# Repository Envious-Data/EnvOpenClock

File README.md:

# Env-OpenClock
 A fancy lil clock using 8x LTP-305s and a Raspberry Pi Pico.

## Information
This clock features a DS3231 but it doesnt have its own onboard battery management meaning its meant to have constant power but there is nothing stopping anyone from soldering something like a pico lipo shim to the back of the PCB. The RTC is mainly for convenience.

There are 4 buttons and a switch, The switch is meant for Summer time adjustment and the 4 buttons are for setting the time or alarm.

## Implemented Features
- Time Setting
- Date Mode

## Planned software features
(Some ideas, may not get implemented)
- Animated text to show time has been set?
- Animated Transition to menus?
- A menu system
- Alarm system
- Text Marquee modes

## Planned Hardware features
In the current version of the board there is a a DS3231 w/ CR1220 battery, Raspberry pi pico, 4x tactile buttons, 4x IS31FL37s, a small piezo speaker and amp and obviously the 8x LTP305 sockets.

We'd like to change this to have easier to press buttons, a larger battery holder, the speaker may not get re-implemented, we'll see when we decide to move toward finalizing the design and preparing for order. Keep in mind that TIL305s have been discontinued for a long time and LTP305s are now discontinued and hard to get so we'll substitute our own "DIY305" which is a dip14 sized PCB with standard headers and 0402 leds but we have made a 0201 version but may not use it due to cost.

## Hardware
I designed the board in KiCad, you can use various plugins to generate production files for your chosen PCB FAB
Some aspects may change but I generally intend to keep the formfactor the same and all the components on one side for cheaper manufacturing.

since the board uses 8x LTP305s you can also display the date instead of the time, the RTC does store the date as well as the time, currently as of writing this the firmware only displays the current time stored on the DS3231 RTC, but the main planned features are day/date/time setting and then goals can expand. Its possible to add text marquee too.

## PCBWAY

[PCBWAY](http://pcbway.com) Kindly sponsored a batch of PCBs of which you can see a video of the board working below

https://github.com/Envious-Data/Env-OpenClock/assets/5001879/fdac6cdb-803a-443c-b91d-f5f40f54c28f

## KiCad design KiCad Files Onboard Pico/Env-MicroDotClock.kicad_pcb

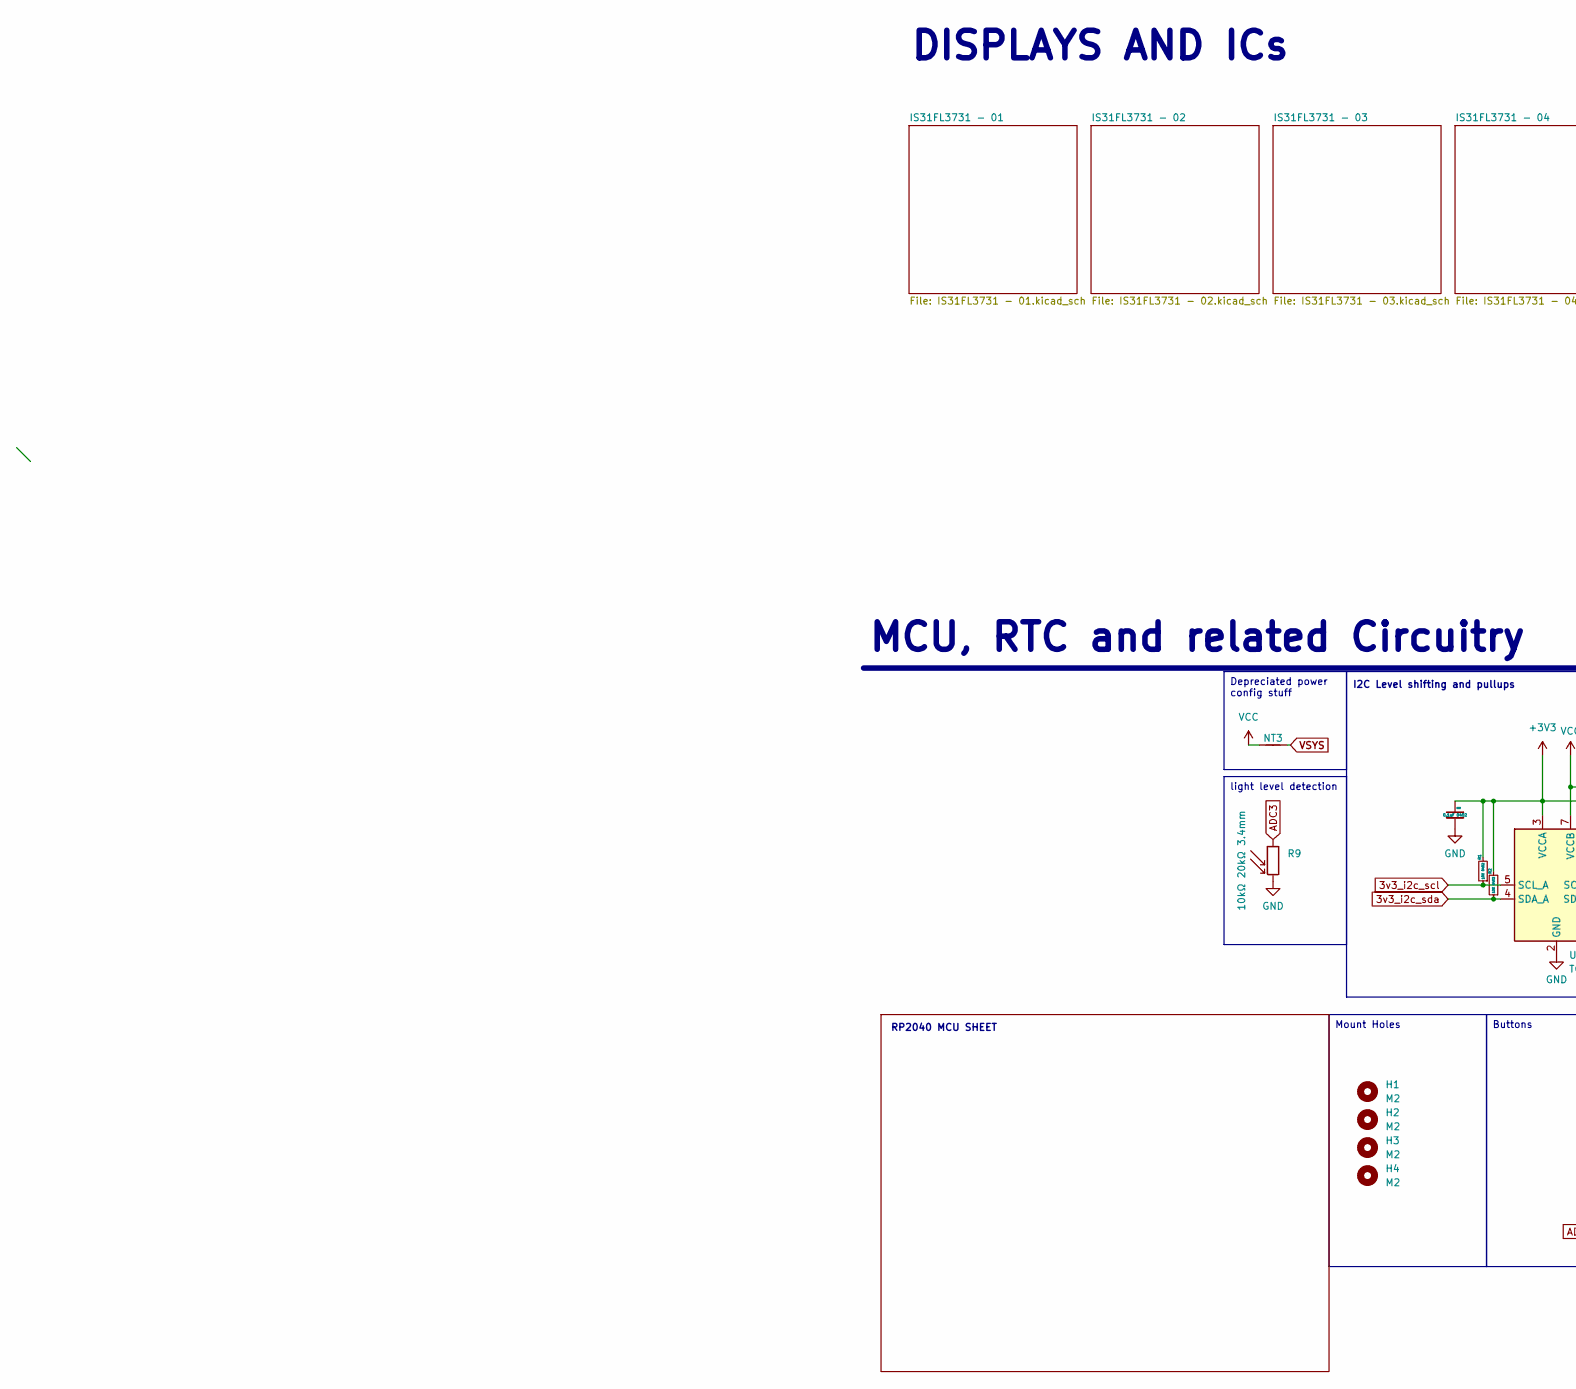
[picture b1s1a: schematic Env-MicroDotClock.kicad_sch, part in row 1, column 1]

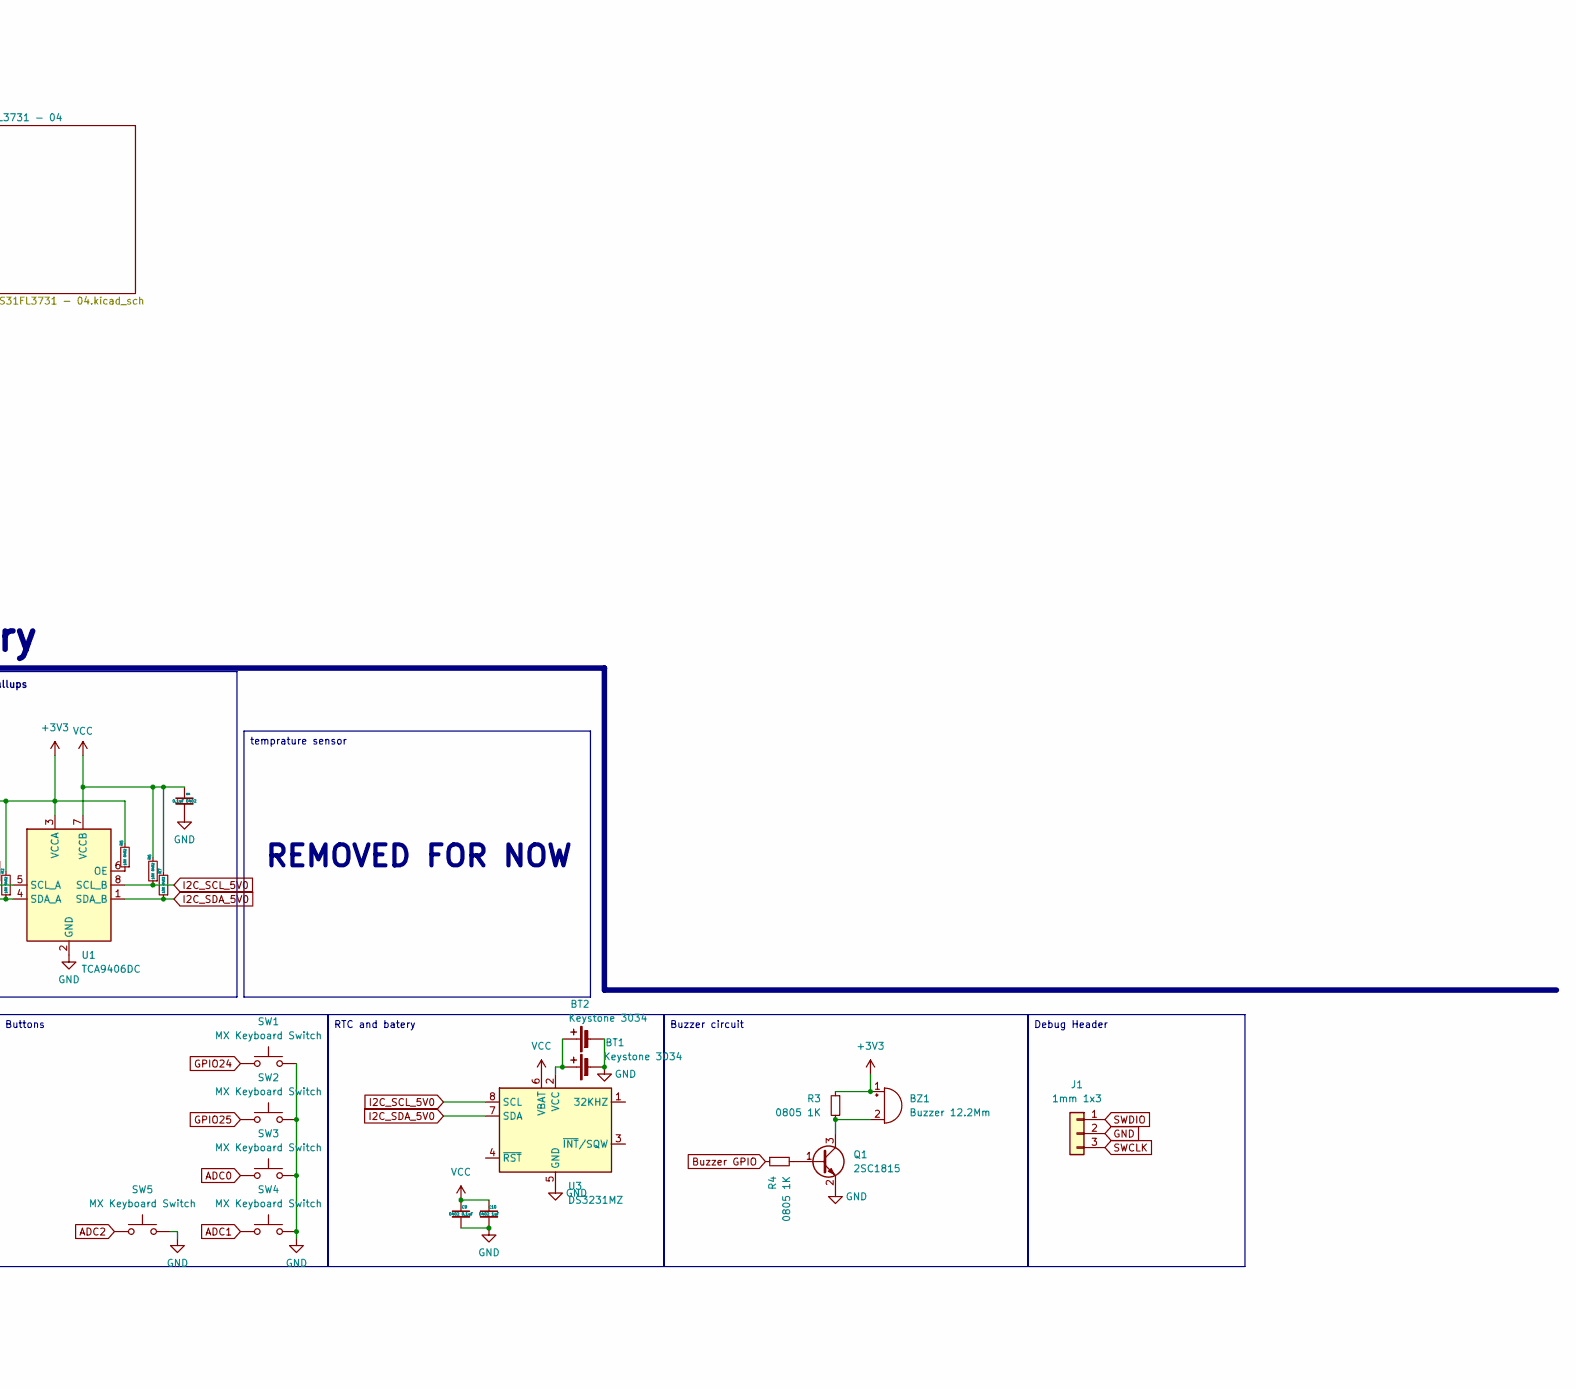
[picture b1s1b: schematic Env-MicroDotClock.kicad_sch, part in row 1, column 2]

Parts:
BT1, BT2: Keystone 3034; BatteryHolder_Keystone_3034_1x20mm
BZ1: Buzzer 12.2Mm; Buzzer_TDK_PS1240P02BT_D12.2mm_H6.5mm
C9: 0402 0.1uF; C_0402_1005Metric
C10: 0402 1uF; C_0402_1005Metric
C33, C34: 0.1uF 0402; C_0402_1005Metric
H1, H2, H3, H4: M2; MountingHole_2.2mm_M2
J1: 1mm 1x3; PinHeader_1x03_P1.00mm_Vertical
NT3: NetTie_2; NetTie-2_THT_Pad0.3mm
Q1: 2SC1815; SOT-23
R1, R2, R5, R6, R7: 10K 0402; R_0402_1005Metric
R3, R4: 0805 1K; R_0805_2012Metric
R9: 10kΩ 20kΩ 3.4mm; R_LDR_5.1x4.3mm_P3.4mm_Vertical
SW1, SW2, SW3, SW4, SW5: MX Keyboard Switch; SW_Cherry_MX_1.00u_PCB
U1: TCA9406DC; VSSOP-8_2.3x2mm_P0.5mm
U3: DS3231MZ; SOIC-8_3.9x4.9mm_P1.27mm

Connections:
3v3_i2c_scl: R1.1, U1.5 (SCL_A); also elsewhere on the board
3v3_i2c_sda: R2.1, U1.4 (SDA_A); also elsewhere on the board
+3V3: BZ1.1 (-), C33.1, R1.2, R2.2, R3.1, R5.2, U1.3 (VCCA); also elsewhere on the board
ADC0: SW3.1; also elsewhere on the board
ADC1: SW4.1; also elsewhere on the board
ADC2: SW5.1; also elsewhere on the board
ADC3: R9.1; also elsewhere on the board
Buzzer GPIO: R4.1; also elsewhere on the board
GND: BT1.2 (-), BT2.2 (-), C9.2, C10.2, C33.2, C34.2, J1.2, Q1.2 (E), R9.2, SW1.2, SW2.2, SW3.2, SW4.2, SW5.2, U1.2 (GND), U3.5 (GND); also elsewhere on the board
GPIO24: SW1.1; also elsewhere on the board
GPIO25: SW2.1; also elsewhere on the board
I2C_SCL_5V0: R6.1, U1.8 (SCL_B), U3.8 (SCL); also elsewhere on the board
I2C_SDA_5V0: R7.1, U1.1 (SDA_B), U3.7 (SDA); also elsewhere on the board
unnamed: BT1.1 (+), BT2.1 (+), U3.2 (VCC)
unnamed: BZ1.2 (+), Q1.3 (C), R3.2
unnamed: Q1.1 (B), R4.2
unnamed: R5.1, U1.6 (OE)
SWCLK: J1.3; also elsewhere on the board
SWDIO: J1.1; also elsewhere on the board
VCC: C9.1, C10.1, C34.1, NT3.1, R6.2, R7.2, U1.7 (VCCB), U3.6 (VBAT); also elsewhere on the board
VSYS: NT3.2; also elsewhere on the board

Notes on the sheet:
light level detection
RTC and batery
Mount Holes
Depreciated power config stuff
Buzzer circuit
Debug Header
Buttons
temprature sensor
DISPLAYS AND ICs
MCU, RTC and related Circuitry
RP2040 MCU SHEET
I2C Level shifting and pullups
REMOVED FOR NOW

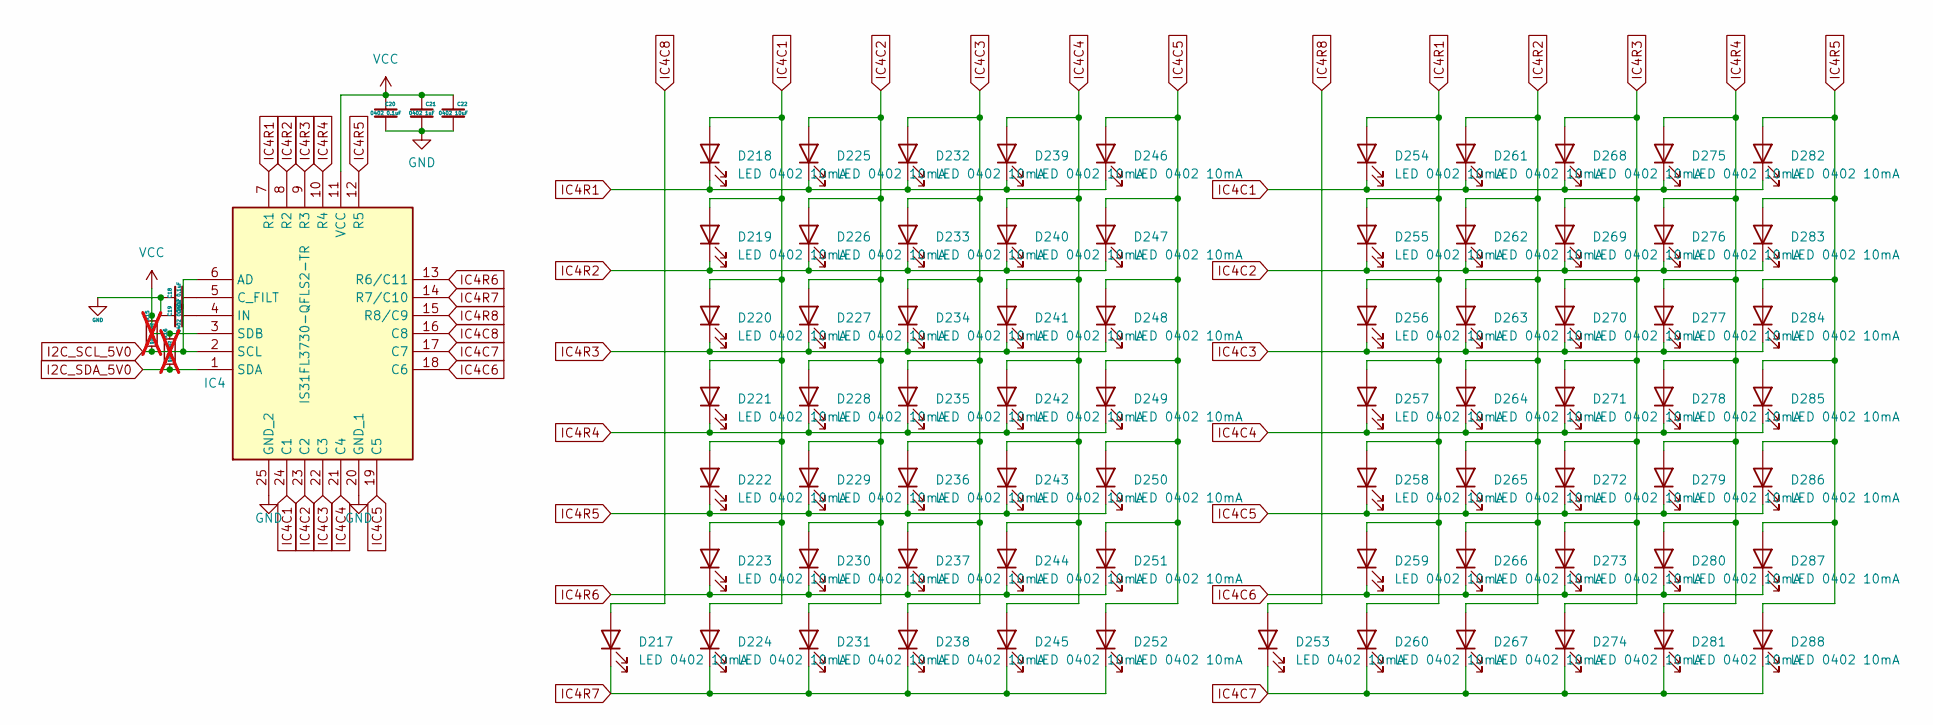
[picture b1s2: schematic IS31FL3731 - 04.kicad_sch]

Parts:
C18, C20: 0402 0.1uF; C_0402_1005Metric
C19: 0402 0.22uF; C_0402_1005Metric
C21: 0402 1uF; C_0402_1005Metric
C22: 0402 10uF; C_0402_1005Metric
D217, D218, D219, D220, D221, D222, D223, D224, D225, D226, D227, D228, D229, D230, D231, D232, D233, D234, D235, D236, D237, D238, D239, D240, D241, D242, D243, D244, D245, D246, D247, D248, D249, D250, D251, D252, D253, D254, D255, D256, D257, D258, D259, D260, D261, D262, D263, D264, D265, D266, D267, D268, D269, D270, D271, D272, D273, D274, D275, D276, D277, D278, D279, D280, D281, D282, D283, D284, D285, D286, D287, D288: LED 0402 10mA; LED_0402_1005Metric
IC4: IS31FL3730-QFLS2-TR; QFN-24-1EP_4x4mm_P0.5mm_EP2.6x2.6mm_ThermalVias; Mouser Part Number 870-IS31FL3730QFLS2R
R15, R16: 10K 0402; R_0402_1005Metric; not fitted

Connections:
GND: C18.1, C19.1, C20.2, C21.2, C22.2, IC4.20 (GND_1), IC4.25 (GND_2); also elsewhere on the board
I2C_SCL_5V0: IC4.2 (SCL), IC4.6 (AD), R15.1; also elsewhere on the board
I2C_SDA_5V0: IC4.1 (SDA), R16.1; also elsewhere on the board
IC4C1: D218.2 (A), D219.2 (A), D220.2 (A), D221.2 (A), D222.2 (A), D223.2 (A), D224.2 (A), D254.1 (K), D261.1 (K), D268.1 (K), D275.1 (K), D282.1 (K), IC4.24 (C1)
IC4C2: D225.2 (A), D226.2 (A), D227.2 (A), D228.2 (A), D229.2 (A), D230.2 (A), D231.2 (A), D255.1 (K), D262.1 (K), D269.1 (K), D276.1 (K), D283.1 (K), IC4.23 (C2)
IC4C3: D232.2 (A), D233.2 (A), D234.2 (A), D235.2 (A), D236.2 (A), D237.2 (A), D238.2 (A), D256.1 (K), D263.1 (K), D270.1 (K), D277.1 (K), D284.1 (K), IC4.22 (C3)
IC4C4: D239.2 (A), D240.2 (A), D241.2 (A), D242.2 (A), D243.2 (A), D244.2 (A), D245.2 (A), D257.1 (K), D264.1 (K), D271.1 (K), D278.1 (K), D285.1 (K), IC4.21 (C4)
IC4C5: D246.2 (A), D247.2 (A), D248.2 (A), D249.2 (A), D250.2 (A), D251.2 (A), D252.2 (A), D258.1 (K), D265.1 (K), D272.1 (K), D279.1 (K), D286.1 (K), IC4.19 (C5)
IC4C6: D259.1 (K), D266.1 (K), D273.1 (K), D280.1 (K), D287.1 (K), IC4.18 (C6)
IC4C7: D253.1 (K), D260.1 (K), D267.1 (K), D274.1 (K), D281.1 (K), D288.1 (K), IC4.17 (C7)
IC4C8: D217.2 (A), IC4.16 (C8)
IC4R1: D218.1 (K), D225.1 (K), D232.1 (K), D239.1 (K), D246.1 (K), D254.2 (A), D255.2 (A), D256.2 (A), D257.2 (A), D258.2 (A), D259.2 (A), D260.2 (A), IC4.7 (R1)
IC4R2: D219.1 (K), D226.1 (K), D233.1 (K), D240.1 (K), D247.1 (K), D261.2 (A), D262.2 (A), D263.2 (A), D264.2 (A), D265.2 (A), D266.2 (A), D267.2 (A), IC4.8 (R2)
IC4R3: D220.1 (K), D227.1 (K), D234.1 (K), D241.1 (K), D248.1 (K), D268.2 (A), D269.2 (A), D270.2 (A), D271.2 (A), D272.2 (A), D273.2 (A), D274.2 (A), IC4.9 (R3)
IC4R4: D221.1 (K), D228.1 (K), D235.1 (K), D242.1 (K), D249.1 (K), D275.2 (A), D276.2 (A), D277.2 (A), D278.2 (A), D279.2 (A), D280.2 (A), D281.2 (A), IC4.10 (R4)
IC4R5: D222.1 (K), D229.1 (K), D236.1 (K), D243.1 (K), D250.1 (K), D282.2 (A), D283.2 (A), D284.2 (A), D285.2 (A), D286.2 (A), D287.2 (A), D288.2 (A), IC4.12 (R5)
IC4R6: D223.1 (K), D230.1 (K), D237.1 (K), D244.1 (K), D251.1 (K), IC4.13 (R6/C11)
IC4R7: D217.1 (K), D224.1 (K), D231.1 (K), D238.1 (K), D245.1 (K), D252.1 (K), IC4.14 (R7/C10)
IC4R8: D253.2 (A), IC4.15 (R8/C9)
unnamed: C18.2, IC4.5 (C_FILT)
unnamed: C19.2, IC4.4 (IN)
VCC: C20.1, C21.1, C22.1, IC4.3 (SDB), IC4.11 (VCC), R15.2, R16.2; also elsewhere on the board

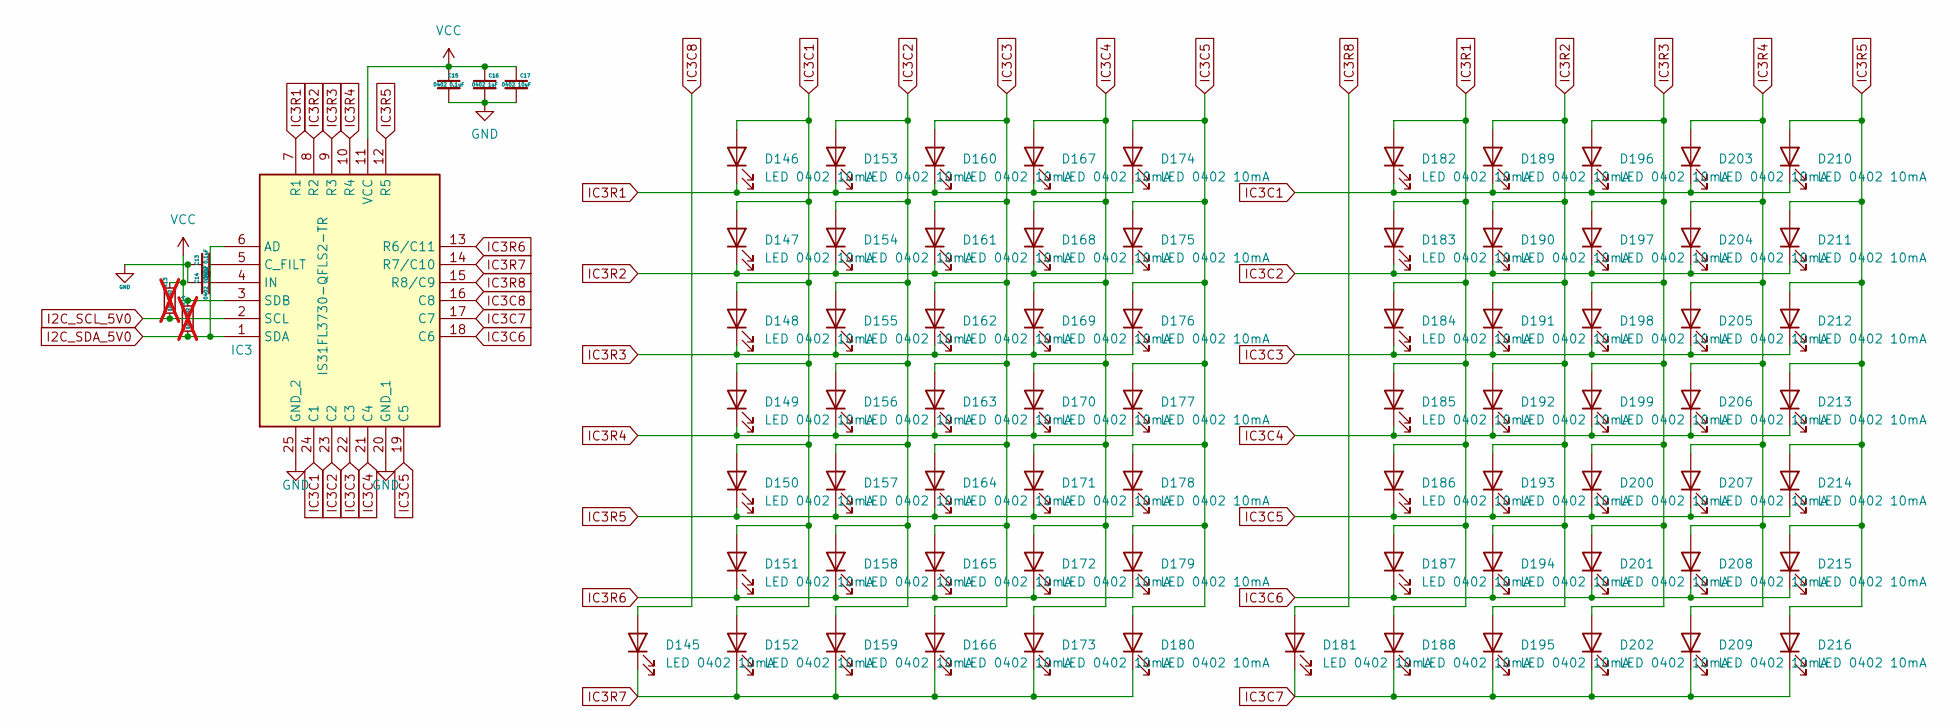
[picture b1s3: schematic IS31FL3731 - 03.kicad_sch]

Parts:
C13, C15: 0402 0.1uF; C_0402_1005Metric
C14: 0402 0.22uF; C_0402_1005Metric
C16: 0402 1uF; C_0402_1005Metric
C17: 0402 10uF; C_0402_1005Metric
D145, D146, D147, D148, D149, D150, D151, D152, D153, D154, D155, D156, D157, D158, D159, D160, D161, D162, D163, D164, D165, D166, D167, D168, D169, D170, D171, D172, D173, D174, D175, D176, D177, D178, D179, D180, D181, D182, D183, D184, D185, D186, D187, D188, D189, D190, D191, D192, D193, D194, D195, D196, D197, D198, D199, D200, D201, D202, D203, D204, D205, D206, D207, D208, D209, D210, D211, D212, D213, D214, D215, D216: LED 0402 10mA; LED_0402_1005Metric
IC3: IS31FL3730-QFLS2-TR; QFN-24-1EP_4x4mm_P0.5mm_EP2.6x2.6mm_ThermalVias; Mouser Part Number 870-IS31FL3730QFLS2R
R13, R14: 10K 0402; R_0402_1005Metric; not fitted

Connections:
GND: C13.1, C14.1, C15.2, C16.2, C17.2, IC3.20 (GND_1), IC3.25 (GND_2); also elsewhere on the board
I2C_SCL_5V0: IC3.2 (SCL), R13.1; also elsewhere on the board
I2C_SDA_5V0: IC3.1 (SDA), IC3.6 (AD), R14.1; also elsewhere on the board
IC3C1: D146.2 (A), D147.2 (A), D148.2 (A), D149.2 (A), D150.2 (A), D151.2 (A), D152.2 (A), D182.1 (K), D189.1 (K), D196.1 (K), D203.1 (K), D210.1 (K), IC3.24 (C1)
IC3C2: D153.2 (A), D154.2 (A), D155.2 (A), D156.2 (A), D157.2 (A), D158.2 (A), D159.2 (A), D183.1 (K), D190.1 (K), D197.1 (K), D204.1 (K), D211.1 (K), IC3.23 (C2)
IC3C3: D160.2 (A), D161.2 (A), D162.2 (A), D163.2 (A), D164.2 (A), D165.2 (A), D166.2 (A), D184.1 (K), D191.1 (K), D198.1 (K), D205.1 (K), D212.1 (K), IC3.22 (C3)
IC3C4: D167.2 (A), D168.2 (A), D169.2 (A), D170.2 (A), D171.2 (A), D172.2 (A), D173.2 (A), D185.1 (K), D192.1 (K), D199.1 (K), D206.1 (K), D213.1 (K), IC3.21 (C4)
IC3C5: D174.2 (A), D175.2 (A), D176.2 (A), D177.2 (A), D178.2 (A), D179.2 (A), D180.2 (A), D186.1 (K), D193.1 (K), D200.1 (K), D207.1 (K), D214.1 (K), IC3.19 (C5)
IC3C6: D187.1 (K), D194.1 (K), D201.1 (K), D208.1 (K), D215.1 (K), IC3.18 (C6)
IC3C7: D181.1 (K), D188.1 (K), D195.1 (K), D202.1 (K), D209.1 (K), D216.1 (K), IC3.17 (C7)
IC3C8: D145.2 (A), IC3.16 (C8)
IC3R1: D146.1 (K), D153.1 (K), D160.1 (K), D167.1 (K), D174.1 (K), D182.2 (A), D183.2 (A), D184.2 (A), D185.2 (A), D186.2 (A), D187.2 (A), D188.2 (A), IC3.7 (R1)
IC3R2: D147.1 (K), D154.1 (K), D161.1 (K), D168.1 (K), D175.1 (K), D189.2 (A), D190.2 (A), D191.2 (A), D192.2 (A), D193.2 (A), D194.2 (A), D195.2 (A), IC3.8 (R2)
IC3R3: D148.1 (K), D155.1 (K), D162.1 (K), D169.1 (K), D176.1 (K), D196.2 (A), D197.2 (A), D198.2 (A), D199.2 (A), D200.2 (A), D201.2 (A), D202.2 (A), IC3.9 (R3)
IC3R4: D149.1 (K), D156.1 (K), D163.1 (K), D170.1 (K), D177.1 (K), D203.2 (A), D204.2 (A), D205.2 (A), D206.2 (A), D207.2 (A), D208.2 (A), D209.2 (A), IC3.10 (R4)
IC3R5: D150.1 (K), D157.1 (K), D164.1 (K), D171.1 (K), D178.1 (K), D210.2 (A), D211.2 (A), D212.2 (A), D213.2 (A), D214.2 (A), D215.2 (A), D216.2 (A), IC3.12 (R5)
IC3R6: D151.1 (K), D158.1 (K), D165.1 (K), D172.1 (K), D179.1 (K), IC3.13 (R6/C11)
IC3R7: D145.1 (K), D152.1 (K), D159.1 (K), D166.1 (K), D173.1 (K), D180.1 (K), IC3.14 (R7/C10)
IC3R8: D181.2 (A), IC3.15 (R8/C9)
unnamed: C13.2, IC3.5 (C_FILT)
unnamed: C14.2, IC3.4 (IN)
VCC: C15.1, C16.1, C17.1, IC3.3 (SDB), IC3.11 (VCC), R13.2, R14.2; also elsewhere on the board

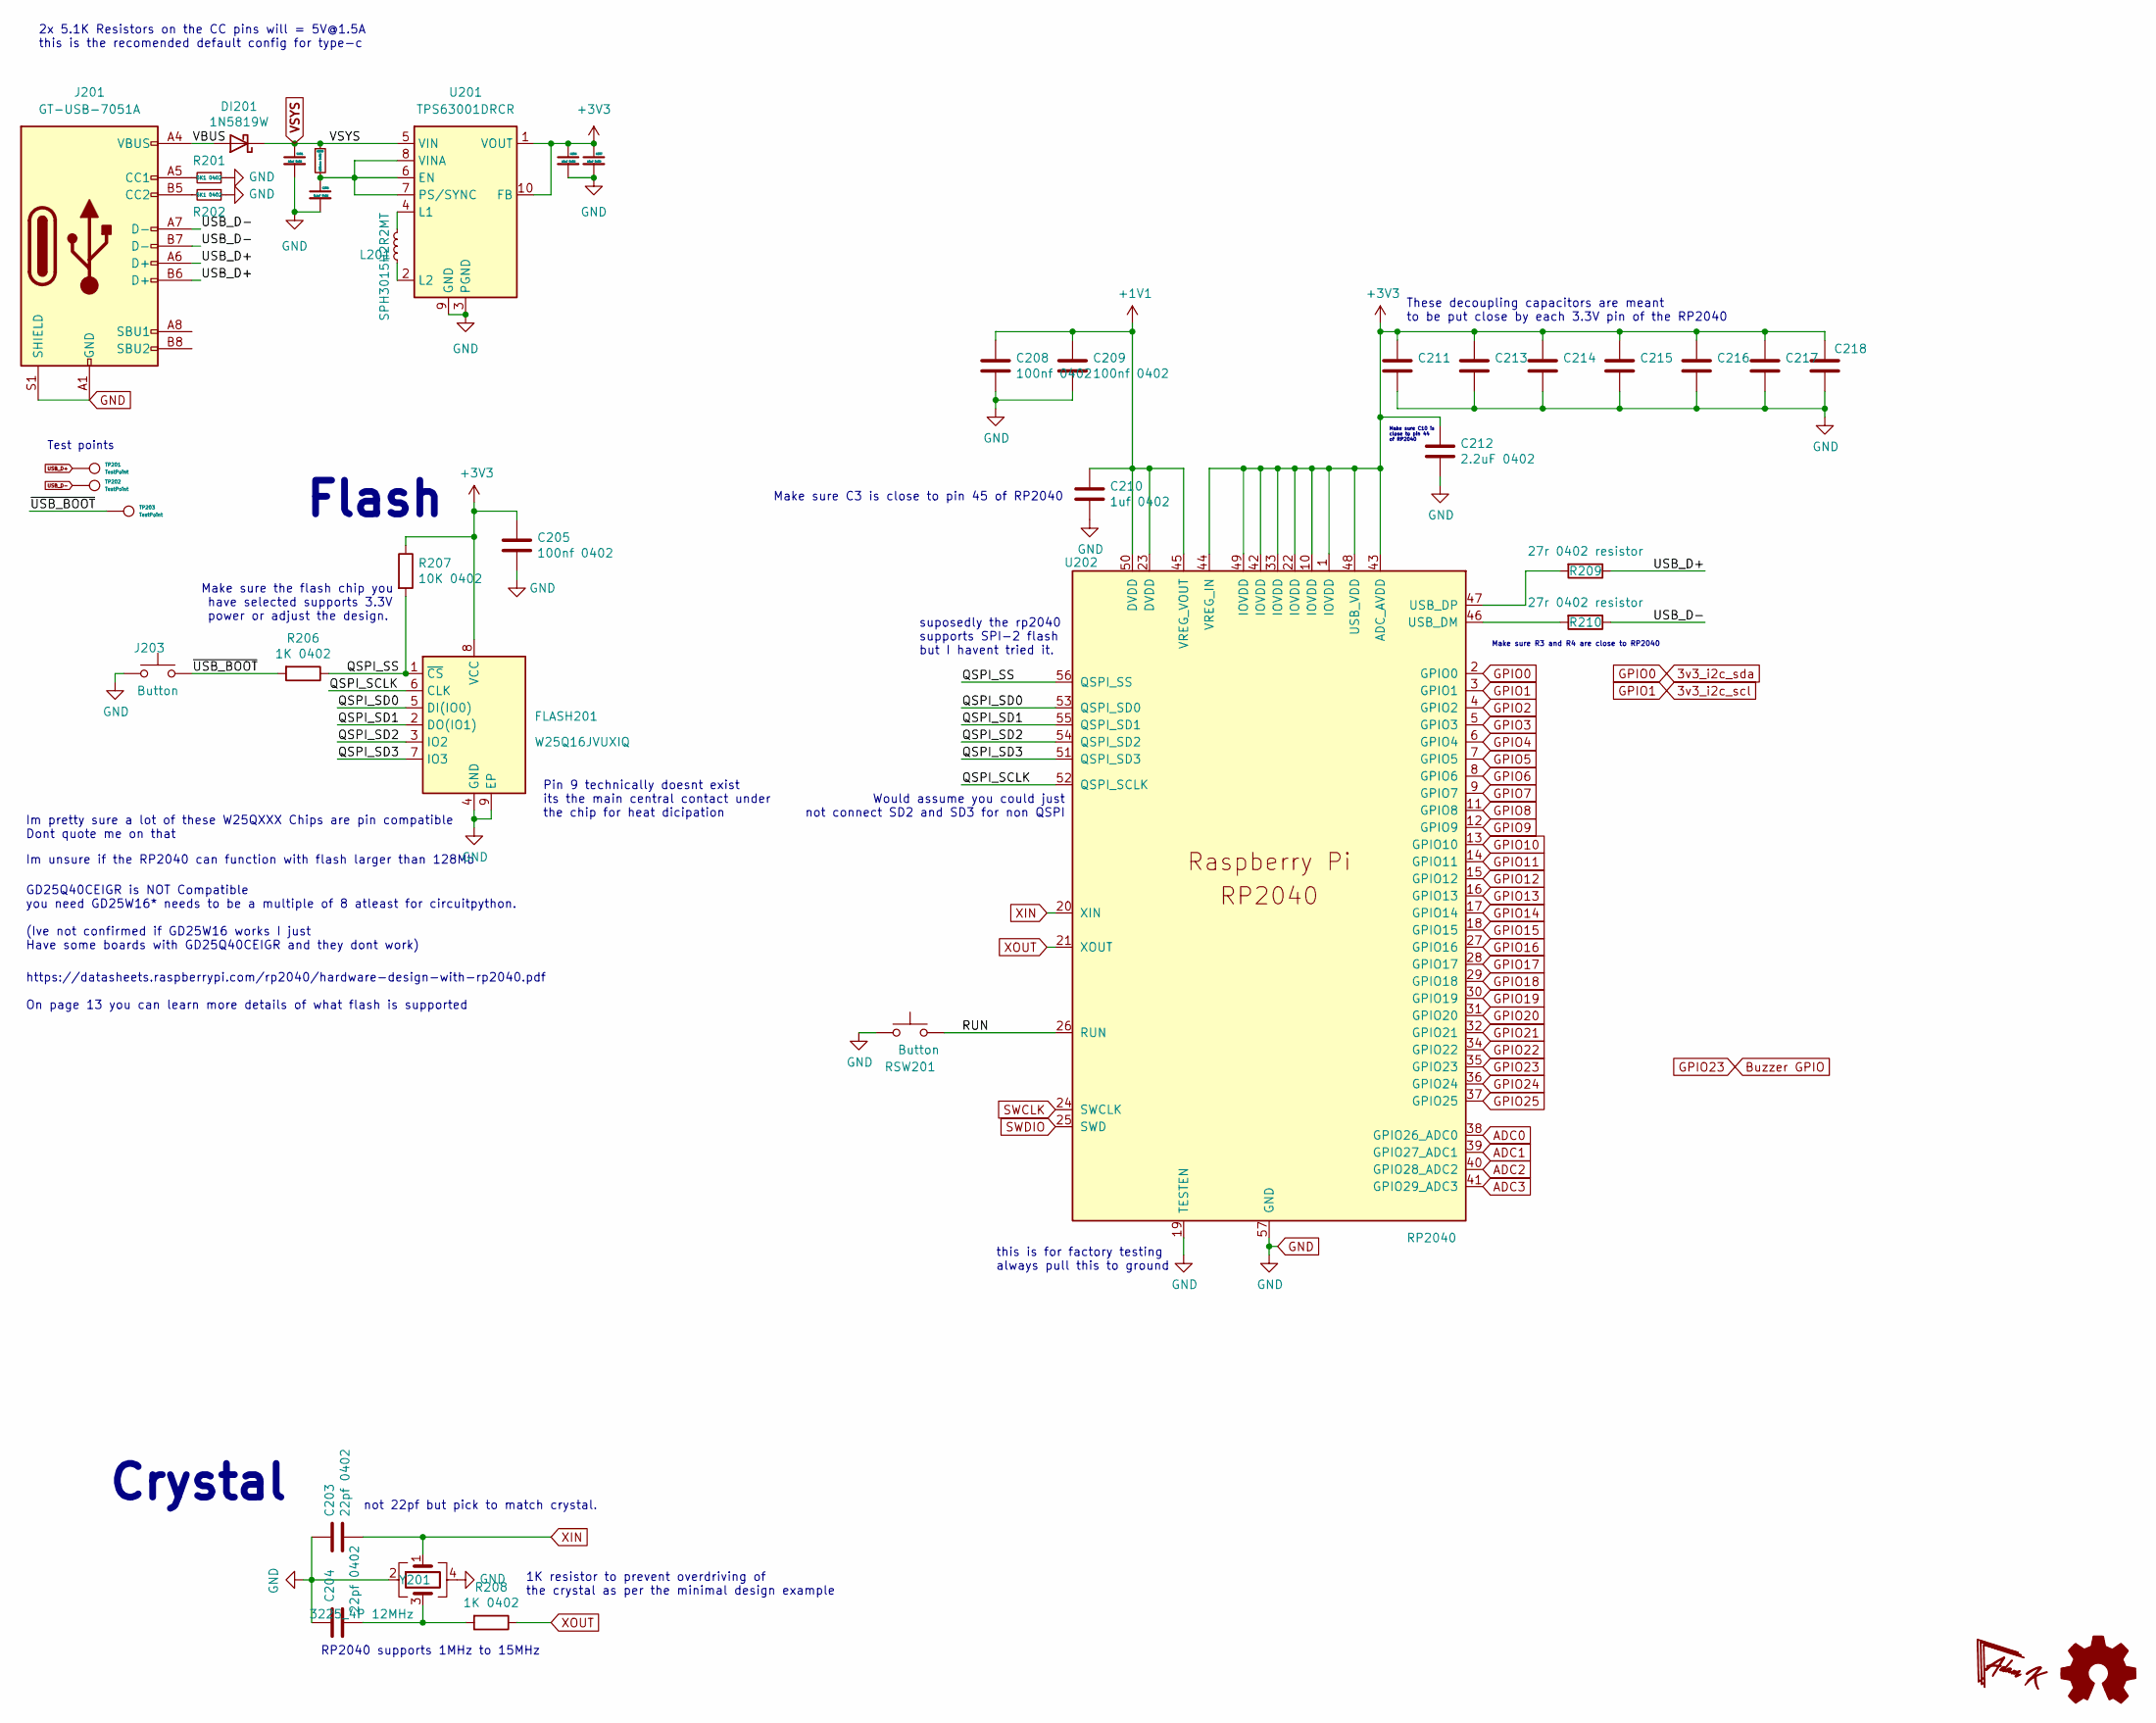
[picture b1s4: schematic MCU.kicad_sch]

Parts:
C201, C206, C207: 10uF 0402; C_0402_1005Metric
C202: 0.1uF 0402; C_0402_1005Metric
C203, C204: 22pf 0402; C_0402_1005Metric
C205, C208, C209, C211, C213, C214, C215, C216, C217, C218: 100nf 0402; C_0402_1005Metric
C210: 1uf 0402; C_0402_1005Metric
C212: 2.2uF 0402; C_0402_1005Metric
DI201: 1N5819W; D_SOD-123
FLASH201: W25Q16JVUXIQ; SON-8-1EP_3x2mm_P0.5mm_EP1.4x1.6mm
J201: GT-USB-7051A; USB_C_Receptacle_G-Switch_GT-USB-7051x
J203: Button; SW_SPST_B3U-1000P-B
L201: SPH3015H2R2MT; L_Sunlord_SWPA3015S
R201, R202: 5K1 0402; R_0402_1005Metric
R205: 100ohm 0402; R_0402_1005Metric
R206, R208: 1K 0402; R_0402_1005Metric
R207: 10K 0402; R_0402_1005Metric
R209, R210: 27r 0402 resistor; R_0402_1005Metric
RSW201: Button; SW_SPST_B3U-1000P-B
TP201, TP202, TP203: TestPoint; TestPoint_Pad_D1.0mm
U201: TPS63001DRCR; Texas_DRC0010J_ThermalVias
U202: RP2040; RP2040-QFN-56; LCSC C2040
Y201: 3225_4P 12MHz; Crystal_SMD_3225-4Pin_3.2x2.5mm

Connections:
3v3_i2c_scl: U202.3 (GPIO1); also elsewhere on the board
3v3_i2c_sda: U202.2 (GPIO0); also elsewhere on the board
+1V1: C208.1, C209.1, C210.1, U202.23 (DVDD), U202.45 (VREG_VOUT), U202.50 (DVDD)
+3V3: C205.1, C206.1, C207.1, C211.1, C212.1, C213.1, C214.1, C215.1, C216.1, C217.1, C218.1, FLASH201.8 (VCC), R207.1, U201.1 (VOUT), U201.10 (FB), U202.1 (IOVDD), U202.10 (IOVDD), U202.22 (IOVDD), U202.33 (IOVDD), U202.42 (IOVDD), U202.43 (ADC_AVDD), U202.44 (VREG_IN), U202.48 (USB_VDD), U202.49 (IOVDD); also elsewhere on the board
/Onboard Pico/QSPI_SCLK: FLASH201.6 (CLK), U202.52 (QSPI_SCLK)
/Onboard Pico/QSPI_SD0: FLASH201.5 (DI(IO0)), U202.53 (QSPI_SD0)
/Onboard Pico/QSPI_SD1: FLASH201.2 (DO(IO1)), U202.55 (QSPI_SD1)
/Onboard Pico/QSPI_SD2: FLASH201.3 (IO2), U202.54 (QSPI_SD2)
/Onboard Pico/QSPI_SD3: FLASH201.7 (IO3), U202.51 (QSPI_SD3)
/Onboard Pico/QSPI_SS: FLASH201.1 (~CS), R206.1, R207.2, U202.56 (QSPI_SS)
/Onboard Pico/RUN: RSW201.2, U202.26 (RUN)
/Onboard Pico/VBUS: DI201.2 (A), J201.A4 (VBUS), J201.A9 (VBUS), J201.B4 (VBUS), J201.B9 (VBUS)
/Onboard Pico/~USB_BOOT: J203.1, R206.2
ADC0: U202.38 (GPIO26_ADC0); also elsewhere on the board
ADC1: U202.39 (GPIO27_ADC1); also elsewhere on the board
ADC2: U202.40 (GPIO28_ADC2); also elsewhere on the board
ADC3: U202.41 (GPIO29_ADC3); also elsewhere on the board
Buzzer GPIO: U202.35 (GPIO23); also elsewhere on the board
GND: C201.2, C202.2, C203.1, C204.1, C205.2, C206.2, C207.2, C208.2, C209.2, C210.2, C211.2, C212.2, C213.2, C214.2, C215.2, C216.2, C217.2, C218.2, FLASH201.4 (GND), FLASH201.9 (EP), J201.A1 (GND), J201.A12 (GND), J201.B1 (GND), J201.B12 (GND), J201.S1 (SHIELD), J203.2, R201.1, R202.1, RSW201.1, U201.3 (PGND), U201.9 (GND), U201.11 (PGND), U202.19 (TESTEN), U202.57 (GND), Y201.2, Y201.4; also elsewhere on the board
GPIO2: U202.4 (GPIO2)
GPIO3: U202.5 (GPIO3)
GPIO4: U202.6 (GPIO4)
GPIO5: U202.7 (GPIO5)
GPIO6: U202.8 (GPIO6)
GPIO7: U202.9 (GPIO7)
GPIO8: U202.11 (GPIO8)
GPIO9: U202.12 (GPIO9)
GPIO10: U202.13 (GPIO10)
GPIO11: U202.14 (GPIO11)
GPIO12: U202.15 (GPIO12)
GPIO13: U202.16 (GPIO13)
GPIO14: U202.17 (GPIO14)
GPIO15: U202.18 (GPIO15)
GPIO16: U202.27 (GPIO16)
GPIO17: U202.28 (GPIO17)
GPIO18: U202.29 (GPIO18)
GPIO19: U202.30 (GPIO19)
GPIO20: U202.31 (GPIO20)
GPIO21: U202.32 (GPIO21)
GPIO22: U202.34 (GPIO22)
GPIO24: U202.36 (GPIO24); also elsewhere on the board
GPIO25: U202.37 (GPIO25); also elsewhere on the board
unnamed: C204.2, R208.2, Y201.3
unnamed: J201.A5 (CC1), R201.2
unnamed: J201.B5 (CC2), R202.2
unnamed: C202.1, R205.2, U201.6 (EN), U201.7 (PS/SYNC), U201.8 (VINA)
unnamed: L201.1, U201.4 (L1)
unnamed: L201.2, U201.2 (L2)
unnamed: R210.2, U202.46 (USB_DM)
unnamed: R209.2, U202.47 (USB_DP)
SWCLK: U202.24 (SWCLK); also elsewhere on the board
SWDIO: U202.25 (SWD); also elsewhere on the board
USB_D+: J201.A6 (D+), J201.B6 (D+), R209.1, TP201.1
USB_D-: J201.A7 (D-), J201.B7 (D-), R210.1, TP202.1
VSYS: C201.1, DI201.1 (K), R205.1, U201.5 (VIN); also elsewhere on the board
XIN: C203.2, U202.20 (XIN), Y201.1
XOUT: R208.1, U202.21 (XOUT)

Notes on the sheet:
GD25Q40CEIGR is NOT Compatible you need GD25W16* needs to be a multiple of 8 atleast for circuitpython. (Ive not confirmed if GD25W16 works I just Have some boards with GD25Q40CEIGR and they dont work)
1K resistor to prevent overdriving of the crystal as per the minimal design example
RP2040 supports 1MHz to 15MHz
https://datasheets.raspberrypi.com/rp2040/hardware-design-with-rp2040.pdf On page 13 you can learn more details of what flash is supported
Flash
Im pretty sure a lot of these W25QXXX Chips are pin compatible Dont quote me on that
suposedly the rp2040 supports SPI-2 flash but I havent tried it.
Would assume you could just not connect SD2 and SD3 for non QSPI
Make sure the flash chip you have selected supports 3.3V power or adjust the design.
Test points
2x 5.1K Resistors on the CC pins will = 5V@1.5A this is the recomended default config for type-c
Im unsure if the RP2040 can function with flash larger than 128Mb
not 22pf but pick to match crystal.
Pin 9 technically doesnt exist its the main central contact under the chip for heat dicipation
These decoupling capacitors are meant to be put close by each 3.3V pin of the RP2040
Crystal
Make sure R3 and R4 are close to RP2040
Make sure C10 is close to pin 44 of RP2040
Make sure C3 is close to pin 45 of RP2040
this is for factory testing always pull this to ground
